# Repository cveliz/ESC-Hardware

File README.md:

# ESC-Hardware
===============

## ESC Schematic

## PCB 3D Model

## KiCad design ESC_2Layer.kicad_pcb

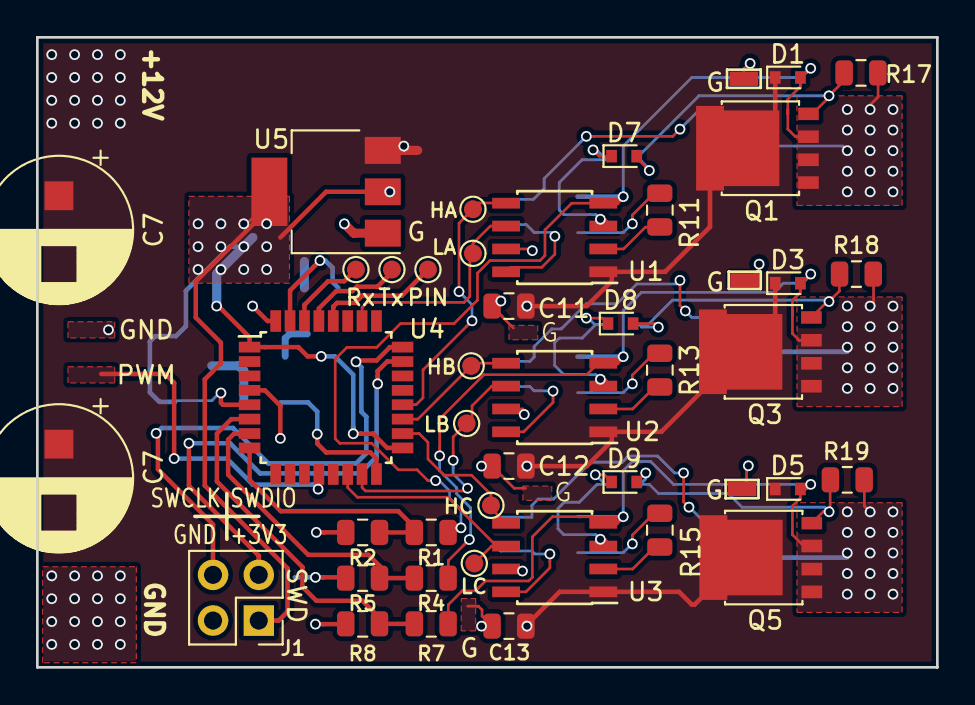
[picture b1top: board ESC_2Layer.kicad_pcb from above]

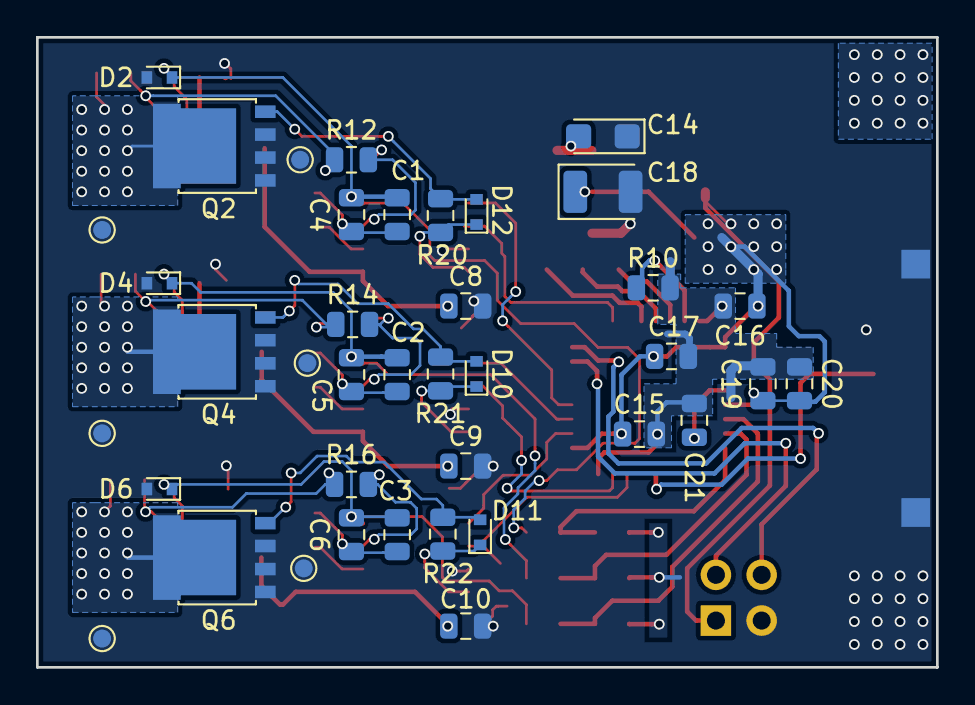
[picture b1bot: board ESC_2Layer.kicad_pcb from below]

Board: 2 copper layers, 50.0 x 35.0 mm, 83 parts (39 on the bottom side), 40 nets.

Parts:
C1, C2, C3, C11, C12, C13, C19: 1u; C_0805_2012Metric
C4, C5, C6, C8, C9, C10, C15, C16, C21: 100n; C_0805_2012Metric
C7, C7#2: 1000u; CP_Radial_D8.0mm_P3.80mm
C14: 10u; CP_EIA-3216-18_Kemet-A
C17: 4.7u; C_0805_2012Metric
C18: 22u; CP_EIA-3528-15_AVX-H
C20: 10n; C_0805_2012Metric
D1, D2, D3, D4, D5, D6, D7, D8, D9, D10, D11, D12: 1N4148; D_SOD-523
J1: SWD; PinHeader_2x02_P2.54mm_Vertical
Q1, Q2, Q3, Q4, Q5, Q6: PSMN011-30YLC; LFPAK56
R1, R4, R7, R10, R17, R18, R19: 10k; R_0805_2012Metric
R2, R5, R8: 2.2k; R_0805_2012Metric
R11, R12, R13, R14, R15, R16, R20, R21, R22: 22R; R_0805_2012Metric
TP1: Q3_G; TestPoint_Pad_D1.0mm
TP2: Q1_G; TestPoint_Pad_D1.0mm
TP3: Q5_G; TestPoint_Pad_D1.0mm
TP4: Q4_G; TestPoint_Pad_D1.0mm
TP5: Q2_G; TestPoint_Pad_D1.0mm
TP6: Q6_G; TestPoint_Pad_D1.0mm
TP7: OB; TestPoint_Pad_D1.0mm
TP8: OA; TestPoint_Pad_D1.0mm
TP9: OC; TestPoint_Pad_D1.0mm
TP10: HA; TestPoint_Pad_D1.0mm
TP11: HB; TestPoint_Pad_D1.0mm
TP12: HC; TestPoint_Pad_D1.0mm
TP13, TP13#2, TP13#3, TP13#4: LA; TestPoint_Pad_D1.0mm
TP14: LB; TestPoint_Pad_D1.0mm
TP15: LC; TestPoint_Pad_D1.0mm
U1, U2, U3: MIC4604; SOIC-8_3.9x4.9mm_P1.27mm
U4: STM32F030K6Tx; LQFP-32_7x7mm_P0.8mm
U5: AP1117-33; SOT-223-3_TabPin2

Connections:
+3V3: C15.1, C16.1, C17.1, C18.1, C19.1, C20.1, J1.1, U4.1, U4.5, U4.17, U5.2
+12V: C7.1, C7#2.1, C8.1, C9.1, C10.1, C11.1, C12.1, C13.1, C14.2, D1.1, D3.1, D5.1, Q1.5, Q3.5, Q5.5, U1.1, U2.1, U3.1, U5.3
/BEMF_A: R1.2, R2.1, U4.8
/BEMF_B: R4.2, R5.1, U4.7
/BEMF_C: R7.2, R8.1, U4.6
/BOOT0: R10.1, U4.31
/DBG_PIN: TP13#3.1, U4.28
/HIGH_A: TP10.1, U1.5, U4.20
/HIGH_B: TP11.1, U2.5, U4.19
/HIGH_C: TP12.1, U3.5, U4.18
/LOW_A: TP13#4.1, U1.6, U4.26
/LOW_B: TP14.1, U2.6, U4.15
/LOW_C: TP15.1, U3.6, U4.14
/NRST: C21.1, U4.4
/OUT_A: C1.2, C4.2, D1.2, D2.1, Q1.1, Q1.2, Q1.3, Q2.5, R1.1, R17.1, U1.4
/OUT_B: C2.2, C5.2, D3.2, D4.1, Q3.1, Q3.2, Q3.3, Q4.5, R4.1, R18.1, U2.4
/OUT_C: C3.2, C6.2, D5.2, D6.1, Q5.1, Q5.2, Q5.3, Q6.5, R7.1, R19.1, U3.4
/SWCLK: J1.4, U4.24
/SWDIO: J1.3, U4.23
/UART1_RX: TP13.1, U4.30
/UART1_TX: TP13#2.1, U4.29
GND: C7.2, C7#2.2, C8.2, C9.2, C10.2, C11.2, C12.2, C13.2, C14.1, C15.2, C16.2, C17.2, C18.2, C19.2, C20.2, C21.2, D2.2, D4.2, D6.2, J1.2, Q2.1, Q2.2, Q2.3, Q4.1, Q4.2, Q4.3, Q6.1, Q6.2, Q6.3, R2.2, R5.2, R8.2, R10.2, TP1.1, TP2.1, TP3.1, TP4.1, TP5.1, TP6.1, TP7.1, TP8.1, TP9.1, U1.7, U2.7, U3.7, U4.16, U4.32, U5.1
unnamed: C1.1, C4.1, R11.1
unnamed: C2.1, C5.1, R13.1
unnamed: C3.1, C6.1, R15.1
unnamed: D7.1, R12.2, U1.3
unnamed: D7.2, Q1.4, R12.1, R17.2
unnamed: D8.1, R14.2, U2.3
unnamed: D8.2, Q3.4, R14.1, R18.2
unnamed: D9.1, R16.2, U3.3
unnamed: D9.2, Q5.4, R16.1, R19.2
unnamed: D10.1, R21.2, U2.8
unnamed: D10.2, Q4.4, R21.1
unnamed: D11.1, R22.2, U3.8
unnamed: D11.2, Q6.4, R22.1
unnamed: D12.1, R20.2, U1.8
unnamed: D12.2, Q2.4, R20.1
unnamed: R11.2, U1.2
unnamed: R13.2, U2.2
unnamed: R15.2, U3.2

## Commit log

2019-04-29 Changes to .gitignore
2019-04-29 Change to images names
2019-04-29 remove images
2019-04-29 Added README file added
2019-07-22 Added PWM input
